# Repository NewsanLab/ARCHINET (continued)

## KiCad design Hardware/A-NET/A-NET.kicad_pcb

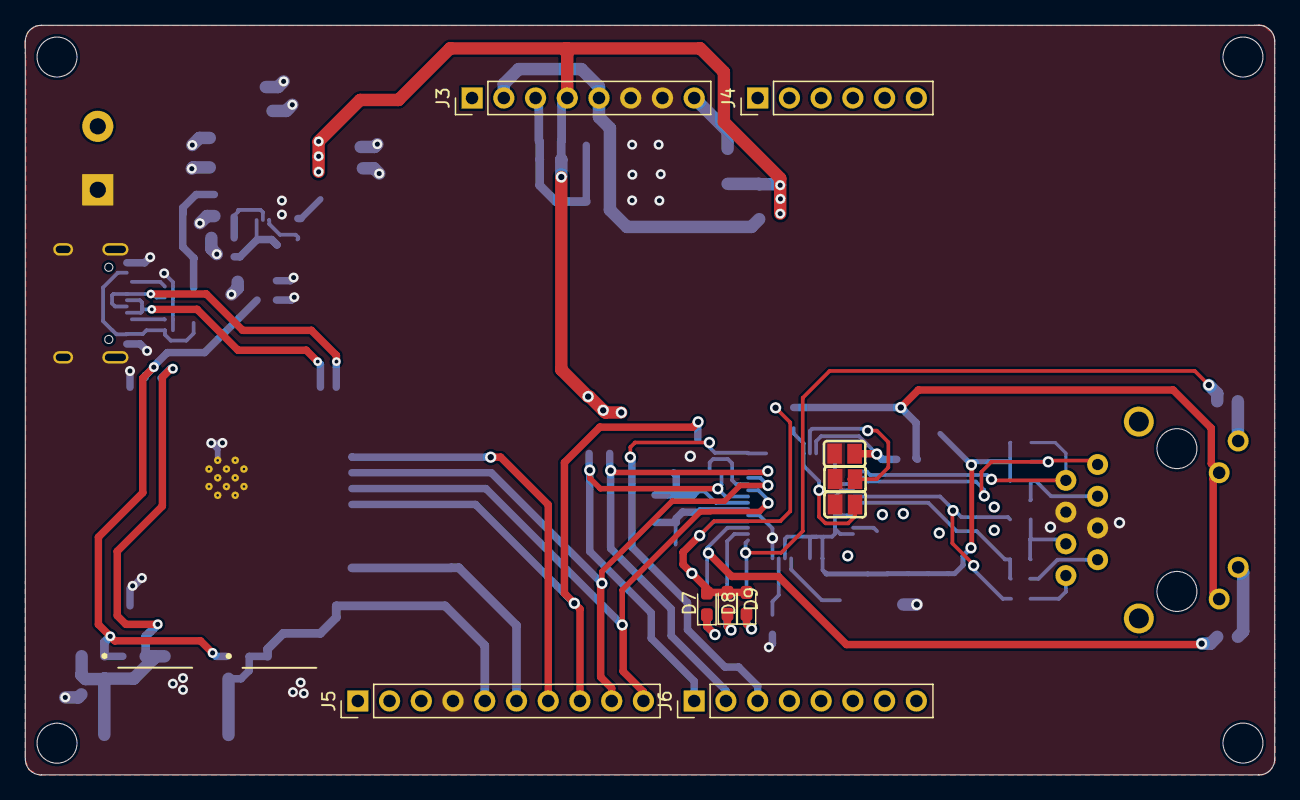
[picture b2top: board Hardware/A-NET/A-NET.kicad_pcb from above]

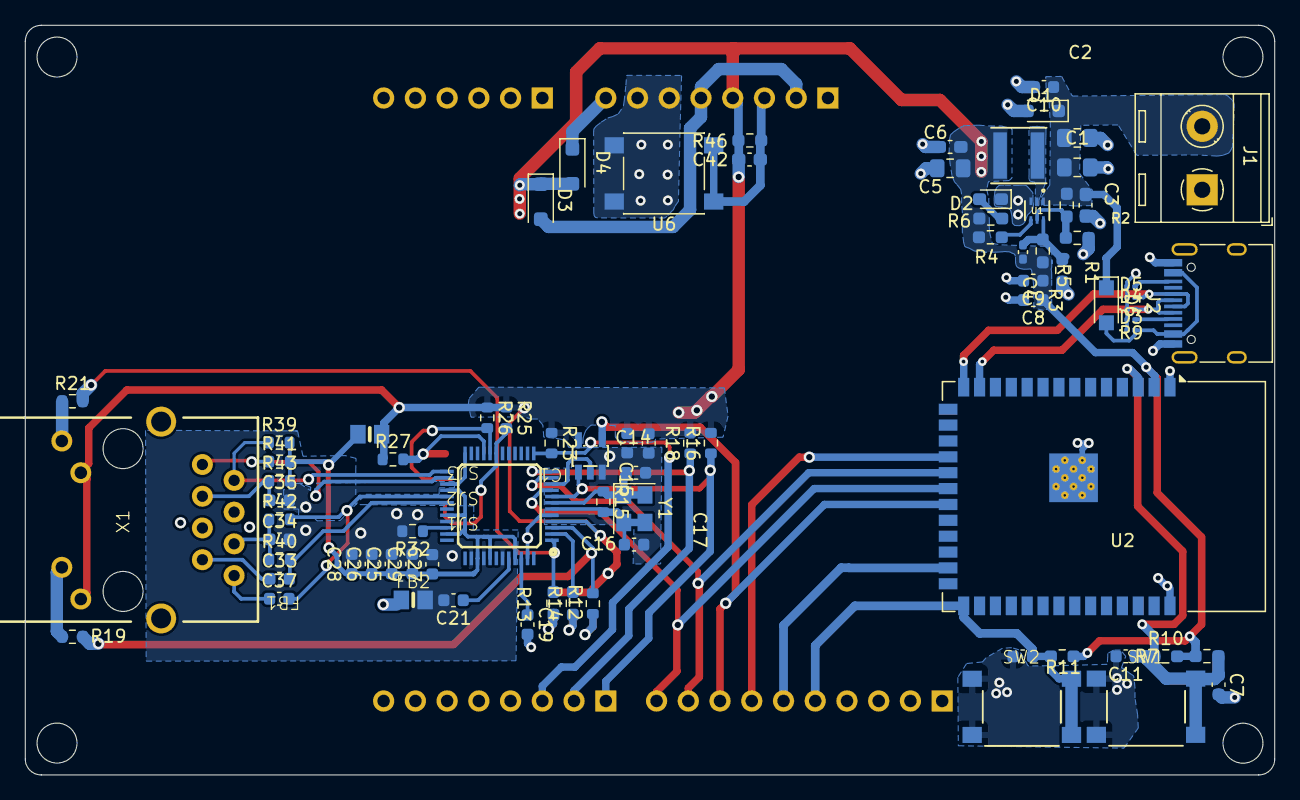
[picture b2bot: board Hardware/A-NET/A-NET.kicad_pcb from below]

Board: 2 copper layers, 100.0 x 60.0 mm, 94 parts (87 on the bottom side), 53 nets.

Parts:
C1, C2: 10u; C_0805_2012Metric_Pad1.18x1.45mm_HandSolder
C3, C6: 100n; C_0603_1608Metric_Pad1.08x0.95mm_HandSolder
C4: 56p; C_0402_1005Metric_Pad0.74x0.62mm_HandSolder
C5: 22u; C_0805_2012Metric_Pad1.18x1.45mm_HandSolder
C7, C9, C10, C11, C12, C15, C21, C29: 10uF; C_0603_1608Metric
C8, C17, C19, C25, C26, C27, C28: 0.1uF; C_0603_1608Metric
C14, C16: 22pF; C_0603_1608Metric
C33, C37: 6.8nF; C_0603_1608Metric
C34, C35: 10nF; C_0603_1608Metric
C42: 1n; C_0603_1608Metric_Pad1.08x0.95mm_HandSolder
D1: SD12C-7; D_SOD-323_HandSoldering
D2, D7, D8, D9: LED_POW; LED_0603_1608Metric_Pad1.05x0.95mm_HandSolder
D3, D4#2, D5: D_TVS_Filled; D_0201_0603Metric
D3#2, D4: DSS14U; D_SOD-123F
D6: 1N5819; Nexperia_CFP3_SOD-123W
FB1, FB2: ferrite; Ferrite
IC1: 74AHC1G125
J1: BAT; TerminalBlock_RND_205-00287_1x02_P5.08mm_Horizontal
J2: USB_C_Receptacle_USB2.0_16P; USB_C_Receptacle_HRO_TYPE-C-31-M-12
J3: Power; PinHeader_1x08_P2.54mm_Vertical
J4: Analog; PinHeader_1x06_P2.54mm_Vertical
J5: Digital/PWM; PinHeader_1x10_P2.54mm_Vertical
J6: Digital/PWM; PinHeader_1x08_P2.54mm_Vertical
L1: 2.2uH; L_2512_6332Metric
MH1, MH2, MH3, MH4: MountingHole_3.2mm
R1: 100K; R_0603_1608Metric_Pad0.98x0.95mm_HandSolder
R2: 32K; R_0603_1608Metric_Pad0.98x0.95mm_HandSolder
R3, R4, R46: 10K; R_0603_1608Metric_Pad0.98x0.95mm_HandSolder
R5: 220K; R_0603_1608Metric_Pad0.98x0.95mm_HandSolder
R6, R7, R10, R11: 1K; R_0603_1608Metric_Pad0.98x0.95mm_HandSolder
R8, R9: 5k1; R_0201_0603Metric
R12, R19, R21: 470; R_0603_1608Metric
R13, R14: 470; R_0603_1608Metric_Pad0.98x0.95mm_HandSolder
R15: 1M; R_0603_1608Metric
R16, R18, R23, R25, R26, R27: 10K; R_0603_1608Metric
R32: 12.4K; R_0603_1608Metric
R39, R40, R41, R42: 49.9; R_0603_1608Metric
R43: 10; R_0603_1608Metric
SJ1, SJ2, SJ3: SOLDERJUMPERREFLOW_NOPASTE; Jumper
SW1, SW2: SW_MEC_5E; button
U1: TPS563252DRLR; SOT6_DRL_TEX-L
U2: ESP32-S3-WROOM-1
U6: RESET; SW_SPST_PTS645
U$1: W5500
X1: RB1-125BAG1A
Y1: 25MHz; Crystal_SMD_TXC_7M-4Pin_3.2x2.5mm

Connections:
+3V3: C4.2, C5.1, C6.1, C8.1, C9.1, C15.1, C17.1, C42.1, D3#2.1 (K), D4.2 (A), D7.2 (A), D8.2 (A), D9.2 (A), FB1.1, IC1.5 (VCC), J3.4, L1.2, R4.2, R5.2, R6.1, R7.2, R10.2, R11.2, R16.2, R18.2, R23.1, R25.1, R26.1, R27.1, R46.2, U2.2 (3V3), U$1.28 (VDD), X1.10 (LED1_K), X1.12 (LED2_A)
+5V: D3#2.2 (A), J3.2, J3.5
/Archi/CS1: J5.7, U2.18 (IO10)
/Archi/MISO: IC1.4 (Y), J5.8, U2.21 (IO13)
/Archi/READY: J5.6, U2.25 (IO48)
/Archi/RUN: C42.2, J3.3, R46.1, U6.1, U6.3
/Ethernet/ACTLED: R12.2, R19.2, U$1.27 (ACTLED)
/Ethernet/CS: IC1.1 (~OE), J6.1, R16.1, U$1.32 (SCSN)
/Ethernet/DUPLED: R14.2, U$1.26 (DUPLED)
/Ethernet/GREENLED: R21.1, X1.9 (LED1_A)
/Ethernet/INTN: J6.2, R18.1, U$1.36 (INTN)
/Ethernet/LINKLED: R13.2, R21.2, U$1.25 (LINKLED)
/Ethernet/MISO: IC1.2 (A), U$1.34 (MISO)
/Ethernet/MOSI: J5.9, U2.19 (IO11), U$1.35 (MOSI)
/Ethernet/RESET: J6.3, R23.2, U$1.37 (RSTN)
/Ethernet/RX+: C33.2, R40.2
/Ethernet/RX-: C37.2, R42.2
/Ethernet/SCK: J5.10, U2.20 (IO12), U$1.33 (SCK)
/Ethernet/TX+: R41.1, X1.1 (TX+)
/Ethernet/TX-: R39.1, X1.2 (TX-)
/Ethernet/YELLOWLED: R19.1, X1.11 (LED2_K)
/MCU-WiFi/CHIP_PU: C7.1, C11.1, R7.1, R10.1, SW1.2, SW1.4, U2.3 (EN)
/MCU-WiFi/D+: D5.2 (A2), J2.A6 (D+), J2.B6 (D+), U2.14 (IO20)
/MCU-WiFi/D-: D4#2.2 (A2), J2.A7 (D-), J2.B7 (D-), U2.13 (IO19)
/MCU-WiFi/GPIO0: C12.1, J5.5, R11.1, SW2.2, SW2.4, U2.27 (IO0)
AGND: C21.2, C25.2, C26.2, C27.2, C28.2, C29.2, C34.2, C35.2, FB2.2, R32.2, U$1.3 (AGND@1), U$1.9 (AGND@2), U$1.14 (AGND@4), U$1.16 (AGND@5), U$1.19 (AGND@6), U$1.48 (AGND@7)
AVDD: C25.1, C26.1, C27.1, C28.1, C29.1, FB1.2, R39.2, R41.2, R43.2, U$1.4 (AVDD@1), U$1.8 (AVDD@2), U$1.11 (AVDD@3), U$1.15 (AVDD@4), U$1.17 (AVDD@5), U$1.21 (AVDD@6)
GND: C1.2, C2.2, C3.2, C5.2, C6.2, C7.2, C8.2, C9.2, C10.2, C11.2, C12.2, C14.2, C15.2, C16.2, C17.2, C19.2, D1.2 (A2), D2.1 (K), D3.1 (A1), D4#2.1 (A1), D5.1 (A1), FB2.1, IC1.3 (GND), J1.1, J2.A1 (GND), J2.A12 (GND), J2.B1 (GND), J2.B12 (GND), J2.S1 (SHIELD), J3.6, J3.7, J5.4, R2.1, R3.1, R8.2, R9.2, SJ1.2 (B), SJ2.2 (B), SJ3.2 (B), SW1.1, SW1.3, SW2.1, SW2.3, U1.3 (GND), U2.1 (GND), U2.40 (GND), U2.41 (GND), U6.2, U6.4, U$1.23 (RSVD(GND)), U$1.29 (GND), X1.4 (GND1), X1.5 (GND2)
unnamed: D2.2 (A), R6.2
unnamed: D3.2 (A2), D6.2 (A), J2.A4 (VBUS), J2.A9 (VBUS), J2.B4 (VBUS), J2.B9 (VBUS)
unnamed: D7.1 (K), R12.1
unnamed: D8.1 (K), R13.1
unnamed: D9.1 (K), R14.1
unnamed: J2.A5 (CC1), R9.1
unnamed: J2.B5 (CC2), R8.1
unnamed: R25.2, SJ1.1 (A), U$1.43 (PMODE2)
unnamed: R26.2, SJ2.1 (A), U$1.44 (PMODE1)
unnamed: R27.2, SJ3.1 (A), U$1.45 (PMODE0)
unnamed: R1.1, R2.2, U1.5 (EN)
unnamed: C4.1, R3.2, R5.1, U1.6 (FB)
unnamed: R4.1, U1.4 (PG)
unnamed: L1.1, U1.2 (SW)
unnamed: C19.1, U$1.22 (1V20)
unnamed: R32.1, U$1.10 (EXRES1)
unnamed: C21.1, U$1.20 (TOCAP)
unnamed: C16.1, R15.2, U$1.30 (XI/CLKIN), Y1.2, Y1.3
unnamed: C14.1, R15.1, U$1.31 (XO), Y1.1, Y1.4
unnamed: C34.1, R40.1, R42.1, X1.6 (RCT)
unnamed: C33.1, X1.7 (RX+)
unnamed: C37.1, X1.8 (RX-)
unnamed: C35.1, R43.1, X1.3 (TCT)
VBAT: C1.1, C2.1, C3.1, C10.1, D1.1 (A1), D6.1 (K), J1.2, R1.2, U1.1 (VIN)
VIN: D4.1 (K), J3.8

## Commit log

2024-10-21 #Libreria SPIS3 | prueba comunicación
2024-10-22 #add service
2024-11-14 add digikey | add POE
2024-11-19 #V.1
2025-04-29 #ejemplos ethernet
2025-06-04 #v1.2
2025-06-11 #add . ejemplo de software
2025-06-11 #add-esp32
2025-06-24 #agregado fin de carrera
2025-06-24 #add html
2025-06-25 .add POST
2025-06-25 .add PING & INFO
2025-06-26 .añadio ejemplos POST,PING,INFO
2025-06-26 .add modificacion funcion ap
2025-06-30 .agregado modificaciones pcb
2025-06-30 .add digikey
2025-06-30 .add digikey-
2025-06-30 .add readme code
2025-06-30 .add readme
2025-07-01 .add readme mod
2025-07-01 .add img
2025-07-01 .add modificaciónes
2025-07-15 .añadio comando UART_OFF + ejemplo
2025-08-15 Rename Group 1.png to diagramaFuente.PNG
2025-08-18 #se actualizo estructura del src esp32
2025-09-25 #BLE_example
2025-09-25 #add BLE code
